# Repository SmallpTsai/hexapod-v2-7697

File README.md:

# hexapod-v2-7697

> 中文版本請看 [這裡](README_tw.md)

Hexapod v2 using Linkit 7697

This is a Hexapod project.

You can use any mobile phone (iOS or Android) to control the movement of hexapod (move foreward, backward, etc...).

See demo video: https://youtu.be/NJ7DdDEcq3U & https://youtu.be/To2Y6Mhu-CE to get the idea.

> More videos can be found at https://smallptsai.github.io/hexapod-web/

## Brief introduction

* **Remote control** is done via `BLE` of `Linkit 7697`
* It has 6 legs, each leg has 3 joint. So there are total `18` **Servo motors** (TowerPro `MG92B`)
* Linkt 7697 dont have so many **PWM control**, so NXP `PCA9685` x 2 are used to control these servo motors
* **Power** comes from a `2S Lipo battery (7.4v)`. Also 7 x `mini360 DC-DC` step down voltage regulator are used. One to provide `5V` to Linkit 7697, The other six to provide `6V` to each legs (1 mini360 serve 3 servo)
* The **body** is 3D printed PLA. I use `Prusa i3 MK2S`, a really good 3D printer.
* Everything (3D STL, PCB schematic, 7697 source code) are included in the project under **GPL license**, Happy making!

## Skill requirement

If you want to make one hexapod by yourself. You should at least knows how to:

* Mechanism part
    * Use `3D printer` to print a model.
    * Able to adjust 3D model to fit your custom need.
* Electronics
    * Make a `PCB` (suggest to use professional PCB services)
    * Soldering `SMD` component (0805 and TSSOP28)
    * How to use/charge/store `LIPO batteries`
* Software
    * Use `Linkit 7697` (ie. upload and run any program)
    * Use `LRemote` to communicate 7697 and your mobile phone

## Table of Content

1. [Mechanism](mechanism/) - How to build the body
1. [Electronics](electronics/) - Circuit explanition
1. [Software](software/) - The software running on Linkit 7697

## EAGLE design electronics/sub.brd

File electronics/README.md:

# Electronics

## Connection Diagram

## Bill of Materials (BOM)

### PCB

Name | Thumbnail | Required | Note |
-------- | --------- | -------- | ---- | 
main |  | 1 |
sub |  | 2 | there is a difference (SJ1) between<br>the 2 PCB, refer to below

### Components

Name | Thumbnail | Required | Note |
-------- | --------- | -------- | ---- | 
[Linkit 7697](https://labs.mediatek.com/zh-tw/platform/linkit-7697) |  | 1 |
[mini360 DC-DC](https://www.aliexpress.com/w/wholesale-mini360-dc-dc.html) Buck voltage regulator |  | 7 | adjust to 5V
[PCA9685](https://cdn-shop.adafruit.com/datasheets/PCA9685.pdf) (TSSOP28)|  | 2 | TSSOP28 |
Resistor: 220 ohm (0805) | | 18 | SMD |
Resistor: 10K ohm (0805) | | 12 | SMD |
Resistor: 470 ohm (0805) | | 1 | SMD |
LED: green or any color (0805) | | 1 | SMD |
Capacitor: 10 uF (0805) | | 2 | SMD |
14 pin 2.54mm female header | | 4 |
4 pin 2.54mm female header | | 2 |
6 pin 2.54mm female header | | 2 |
4 pin 2.54mm 90 degress male header | | 2 |
6 pin 2.54mm 90 degress male header | | 2 |
4 pin 2.54mm male header | | 2 |
3 pin 2.54mm male header (black) | | 6 |
3 pin 2.54mm male header (yellow) | | 6 |
3 pin 2.54mm male header (red) | | 6 |
2 pin 2.54mm male header | | 1 |
Jumper 2.54mm | | 1 |

## PCB detail

##### Software 

Please use **Eagle 7.7** software to open schematic files (main.sch/main.brd and sub.sch/sub.brd)

Eagle 7.7 can be found at http://eagle.autodesk.com/eagle/software-versions/1

    Note.
    7.7 is an old and free version of Eagle. 
    Latest Eagle is not free anymore unless you are students

##### Manufacture

There are a lot of online service that can manufacture PCB/PCBA for you (just google `PCB/PCBA`).

Seeed (https://www.seeedstudio.io/fusion_pcb.html) is one of them.

They also provide instructions of generating necessary Gerber files at http://support.seeedstudio.com/knowledgebase/articles/1176532-how-to-generate-gerber-file.

### Main

`main.brd`/`main.sch`

##### Schematic

    Note.
    `MP2307` refer to mini360 DC-DC converter

##### Layout

##### PCB

### Sub (x2)

`sub.brd`/`usb.sch`

> There is 1 difference between left and right PCB. The SJ1 of right PCB is left open, but `SJ1` of left PCB should be **closed**. (This is i2c address setting of PCB9865)

##### Schematic

    Note.
    `MP2307` refer to mini360 DC-DC converter

##### Layout

##### PCB

## Servo Connection

Each leg of hexapod has 3 servos (body, thigh, foot), refer to below diagram for correct connection

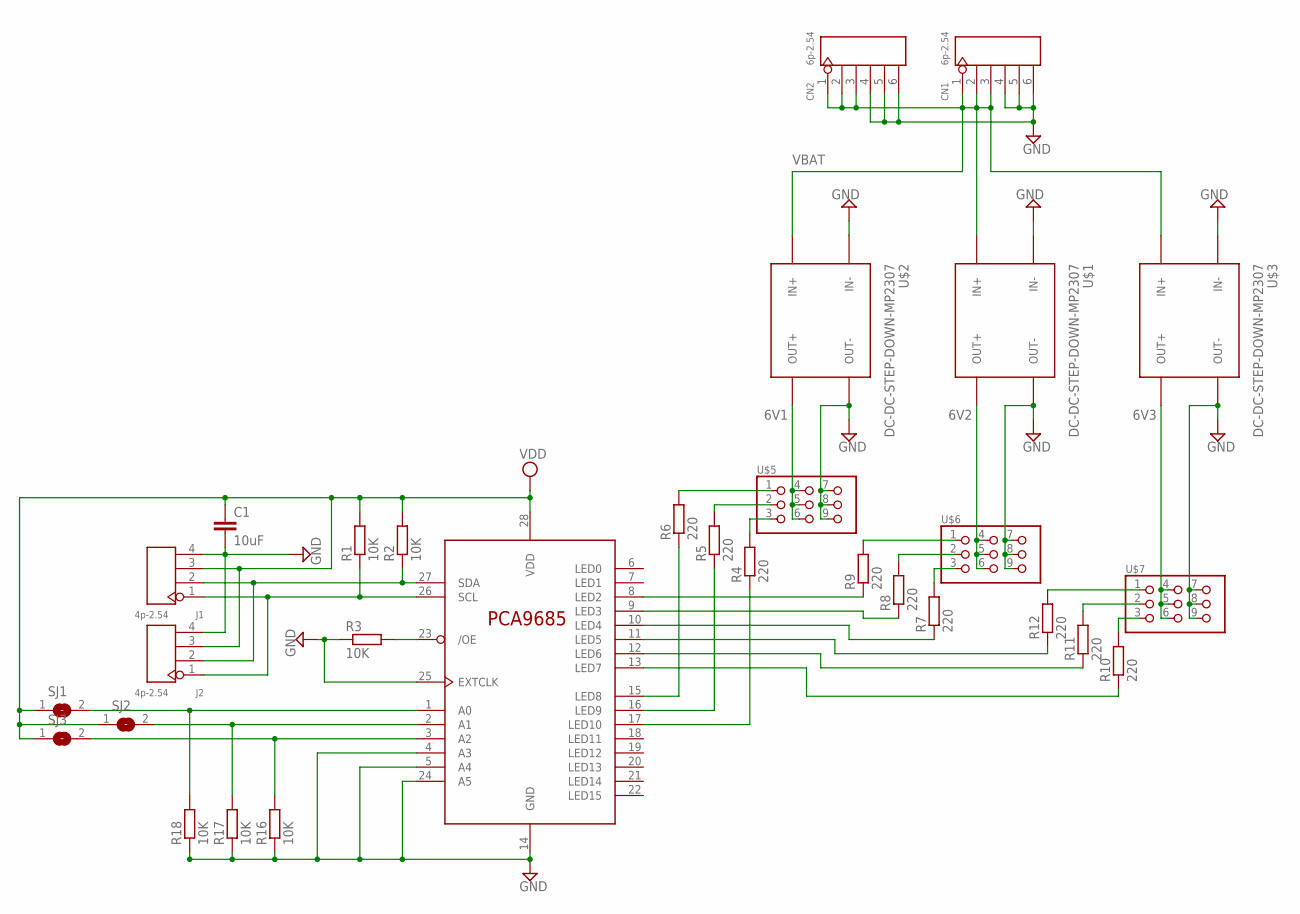
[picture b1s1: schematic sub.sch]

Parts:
C1: 10uF; C0805
CN1, CN2: 6p-2.54; H6-2.54
J1, J2: 4p-2.54; H4-2.54
R1, R2, R3, R16, R17, R18: 10K; M0805
R4, R5, R6, R7, R8, R9, R10, R11, R12: 220; M0805
SJ1, SJ2, SJ3: SJ
U$1, U$2, U$3: DC-DC-STEP-DOWN-MP2307
U$4: PCA9685PW; TSSOP28
U$5, U$6, U$7: PIN_3X3

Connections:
6V1: U$2.OUT+, U$5.4, U$5.5, U$5.6
6V2: U$1.OUT+, U$6.4, U$6.5, U$6.6
6V3: U$3.OUT+, U$7.4, U$7.5, U$7.6
GND: C1.2, CN1.4, CN1.5, CN1.6, CN2.4, CN2.5, CN2.6, J1.4, J2.4, R3.1, R16.1, R17.1, R18.1, U$1.IN-, U$1.OUT-, U$2.IN-, U$2.OUT-, U$3.IN-, U$3.OUT-, U$4.4 (A3), U$4.5 (A4), U$4.14 (GND), U$4.24 (A5), U$4.25 (EXTCLK), U$5.7, U$5.8, U$5.9, U$6.7, U$6.8, U$6.9, U$7.7, U$7.8, U$7.9
unnamed: J1.1, J2.1, R1.1, U$4.26 (SCL)
unnamed: R6.1, U$4.15 (LED8)
unnamed: R3.2, U$4.23 (/OE)
unnamed: R5.1, U$4.16 (LED9)
unnamed: R4.1, U$4.17 (LED10)
unnamed: R9.1, U$4.8 (LED2)
unnamed: R8.1, U$4.9 (LED3)
unnamed: R7.1, U$4.10 (LED4)
unnamed: R11.1, U$4.12 (LED6)
unnamed: R4.2, U$5.3
unnamed: R5.2, U$5.2
unnamed: R6.2, U$5.1
unnamed: R9.2, U$6.1
unnamed: R8.2, U$6.2
unnamed: R7.2, U$6.3
unnamed: R10.1, U$4.13 (LED7)
unnamed: R12.1, U$4.11 (LED5)
unnamed: R12.2, U$7.1
unnamed: R11.2, U$7.2
unnamed: R10.2, U$7.3
unnamed: R16.2, SJ3.2, U$4.3 (A2)
unnamed: R17.2, SJ2.2, U$4.2 (A1)
unnamed: R18.2, SJ1.2, U$4.1 (A0)
unnamed: J1.2, J2.2, R2.1, U$4.27 (SDA)
VBAT: CN1.1, CN1.2, CN1.3, CN2.1, CN2.2, CN2.3, U$1.IN+, U$2.IN+, U$3.IN+
VDD: C1.1, J1.3, J2.3, R1.2, R2.2, SJ1.1, SJ2.1, SJ3.1, U$4.28 (VDD)

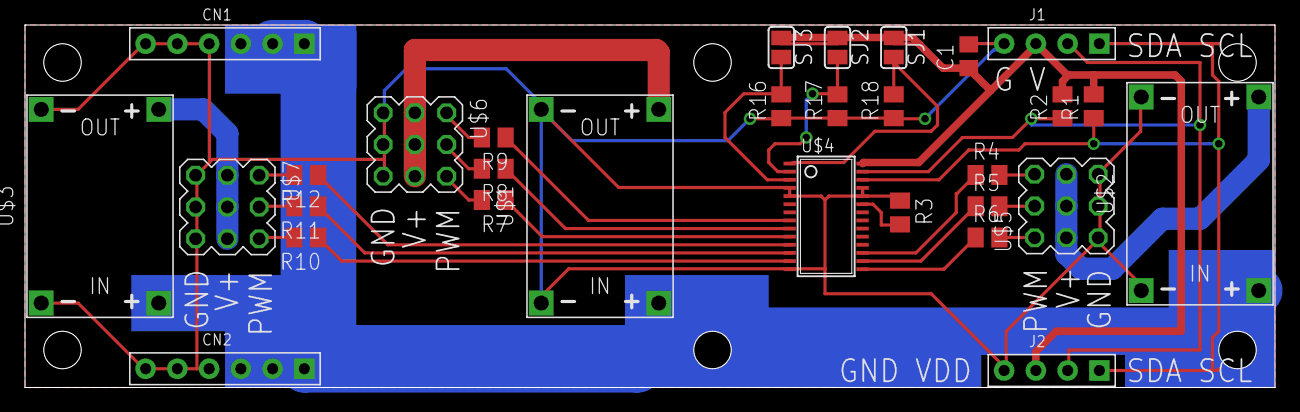
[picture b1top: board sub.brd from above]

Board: 2 copper layers, 100.0 x 29.0 mm, 30 parts (0 on the bottom side), 30 nets.

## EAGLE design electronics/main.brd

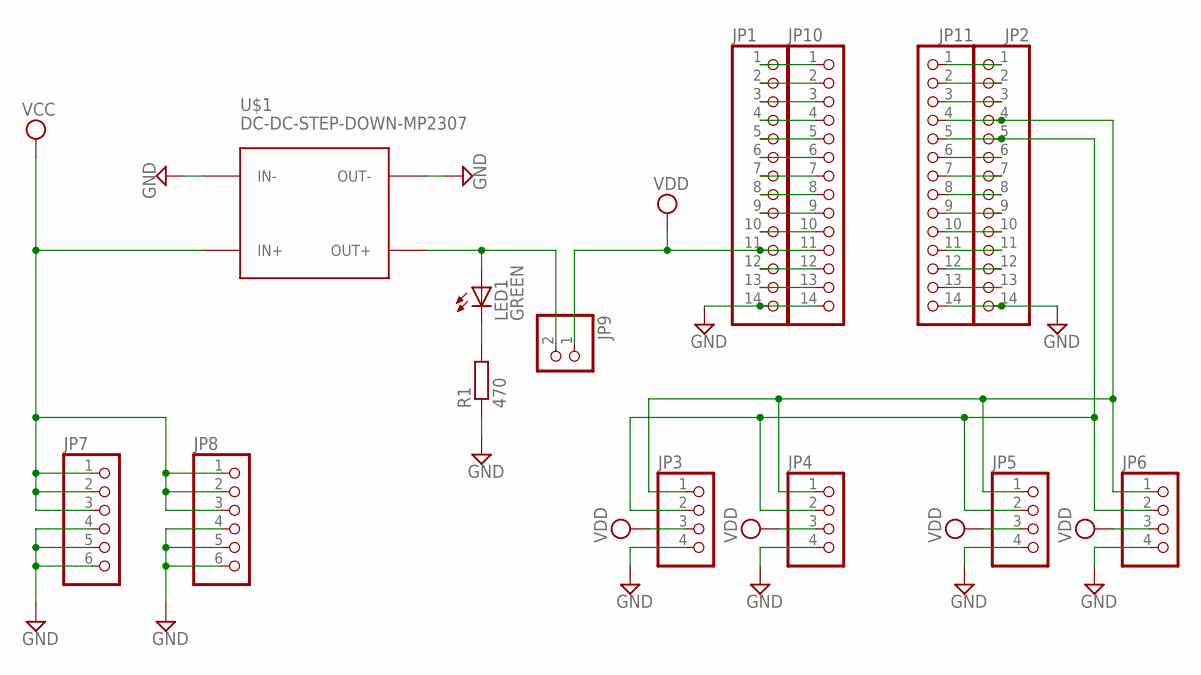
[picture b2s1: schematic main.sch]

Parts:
JP1, JP2, JP10, JP11: PINHD-1X14_2.54; 1X14
JP3, JP4: PINHD-1X4_2.54-90°; 1X04/90
JP5, JP6: PINHD-1X4_2.54; 1X04
JP7, JP8: PINHD-1X6_2.54-90°; 1X06/90
JP9: PINHD-1X2_2.54; 1X02
LED1: GREEN; CHIP-LED0805
R1: 470; R0805
U$1: DC-DC-STEP-DOWN-MP2307

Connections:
+5V: JP9.2, LED1.A, U$1.OUT+
GND: JP1.14, JP2.14, JP3.4, JP4.4, JP5.4, JP6.4, JP7.4, JP7.5, JP7.6, JP8.4, JP8.5, JP8.6, JP10.14, JP11.14, R1.1, U$1.IN-, U$1.OUT-
unnamed: JP1.1, JP10.1
unnamed: JP1.2, JP10.2
unnamed: JP1.3, JP10.3
unnamed: LED1.C, R1.2
unnamed: JP1.4, JP10.4
unnamed: JP1.5, JP10.5
unnamed: JP1.6, JP10.6
unnamed: JP1.7, JP10.7
unnamed: JP1.8, JP10.8
unnamed: JP1.9, JP10.9
unnamed: JP1.10, JP10.10
unnamed: JP1.12, JP10.12
unnamed: JP1.13, JP10.13
unnamed: JP2.1, JP11.1
unnamed: JP2.2, JP11.2
unnamed: JP2.3, JP11.3
unnamed: JP2.6, JP11.6
unnamed: JP2.7, JP11.7
unnamed: JP2.8, JP11.8
unnamed: JP2.9, JP11.9
unnamed: JP2.10, JP11.10
unnamed: JP2.11, JP11.11
unnamed: JP2.12, JP11.12
unnamed: JP2.13, JP11.13
SCL: JP2.4, JP3.1, JP4.1, JP5.1, JP6.1, JP11.4
SDA: JP2.5, JP3.2, JP4.2, JP5.2, JP6.2, JP11.5
VCC: JP7.1, JP7.2, JP7.3, JP8.1, JP8.2, JP8.3, U$1.IN+
VDD: JP1.11, JP3.3, JP4.3, JP5.3, JP6.3, JP9.1, JP10.11

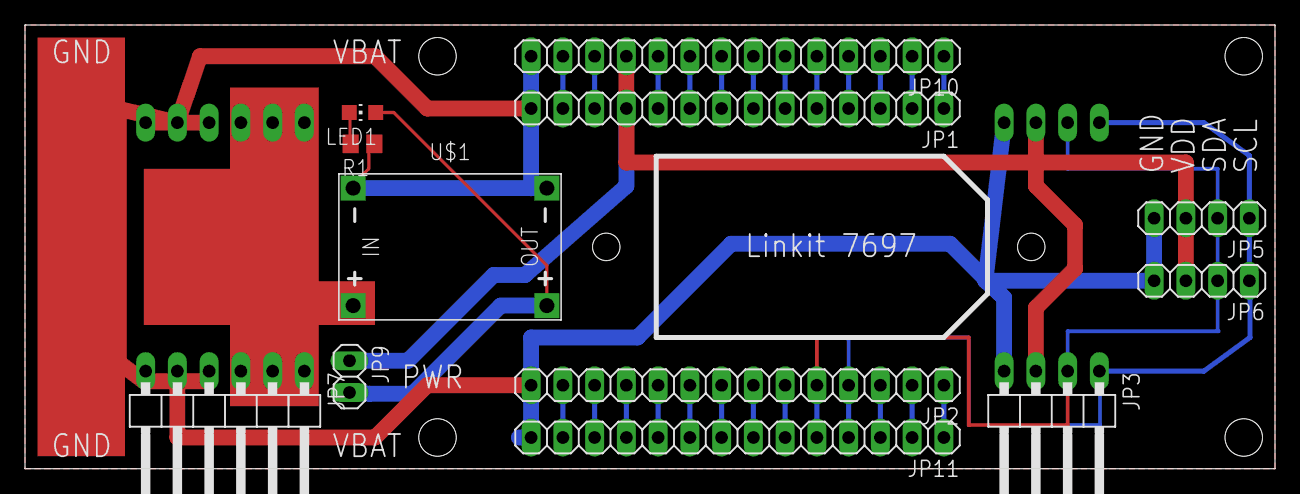
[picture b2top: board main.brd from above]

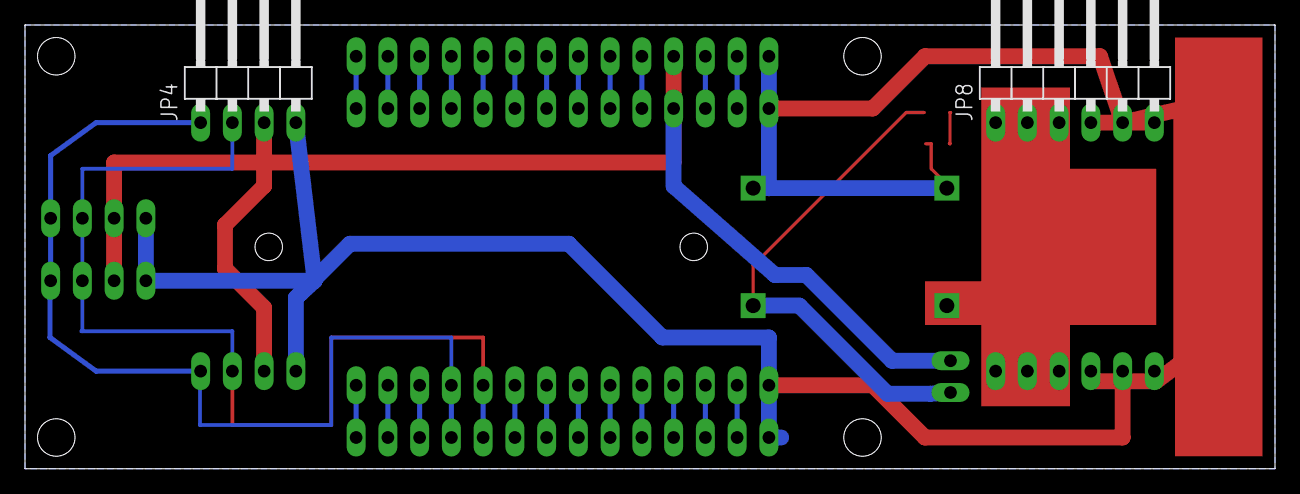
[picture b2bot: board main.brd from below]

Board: 2 copper layers, 100.0 x 35.5 mm, 14 parts (2 on the bottom side), 30 nets.

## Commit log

2018-09-20 mechanism part documentation
2018-09-21 add screw part
2018-09-21 add more thumbnail
2018-09-21 add more parts
2018-09-23 add more BOM images
2018-10-06 add sch and src
2018-10-07 add stl part
2018-10-08 add leg assemble instruction
2018-10-10 add run/climb movement
2018-10-10 add UI screenshot
2018-10-14 add docs folder
2018-10-14 modify README
2018-12-09 update to lock-based joint
2019-01-10 add more docs
2019-01-24 add zhTw readme & update some manual
2019-03-23 update web content
2019-03-23 update web content (portrait support, metas)
2019-03-23 add google search verification
2019-03-23 add more google search verification
2019-03-24 update web url
2019-05-15 Added fixed joint_cross.stl by jmfinn9
2019-05-15 Fixed leg_bottom.stl
2019-06-15 update video link

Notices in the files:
parts and their libraries:
diy-modules: Released under the Creative Commons Attribution 4.0 International License: http://creativecommons.org/licenses/by/4.0
